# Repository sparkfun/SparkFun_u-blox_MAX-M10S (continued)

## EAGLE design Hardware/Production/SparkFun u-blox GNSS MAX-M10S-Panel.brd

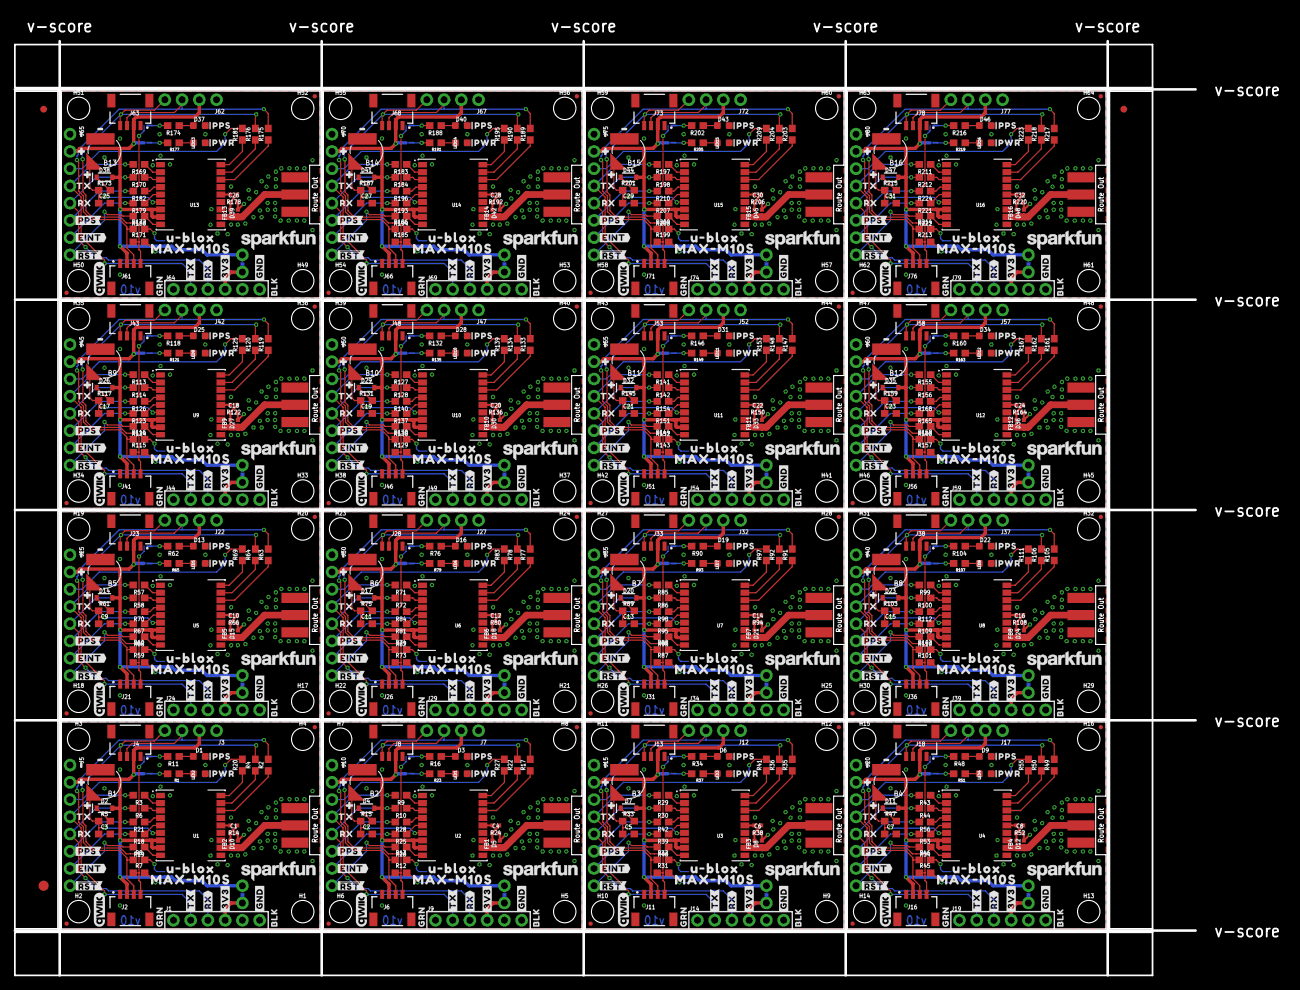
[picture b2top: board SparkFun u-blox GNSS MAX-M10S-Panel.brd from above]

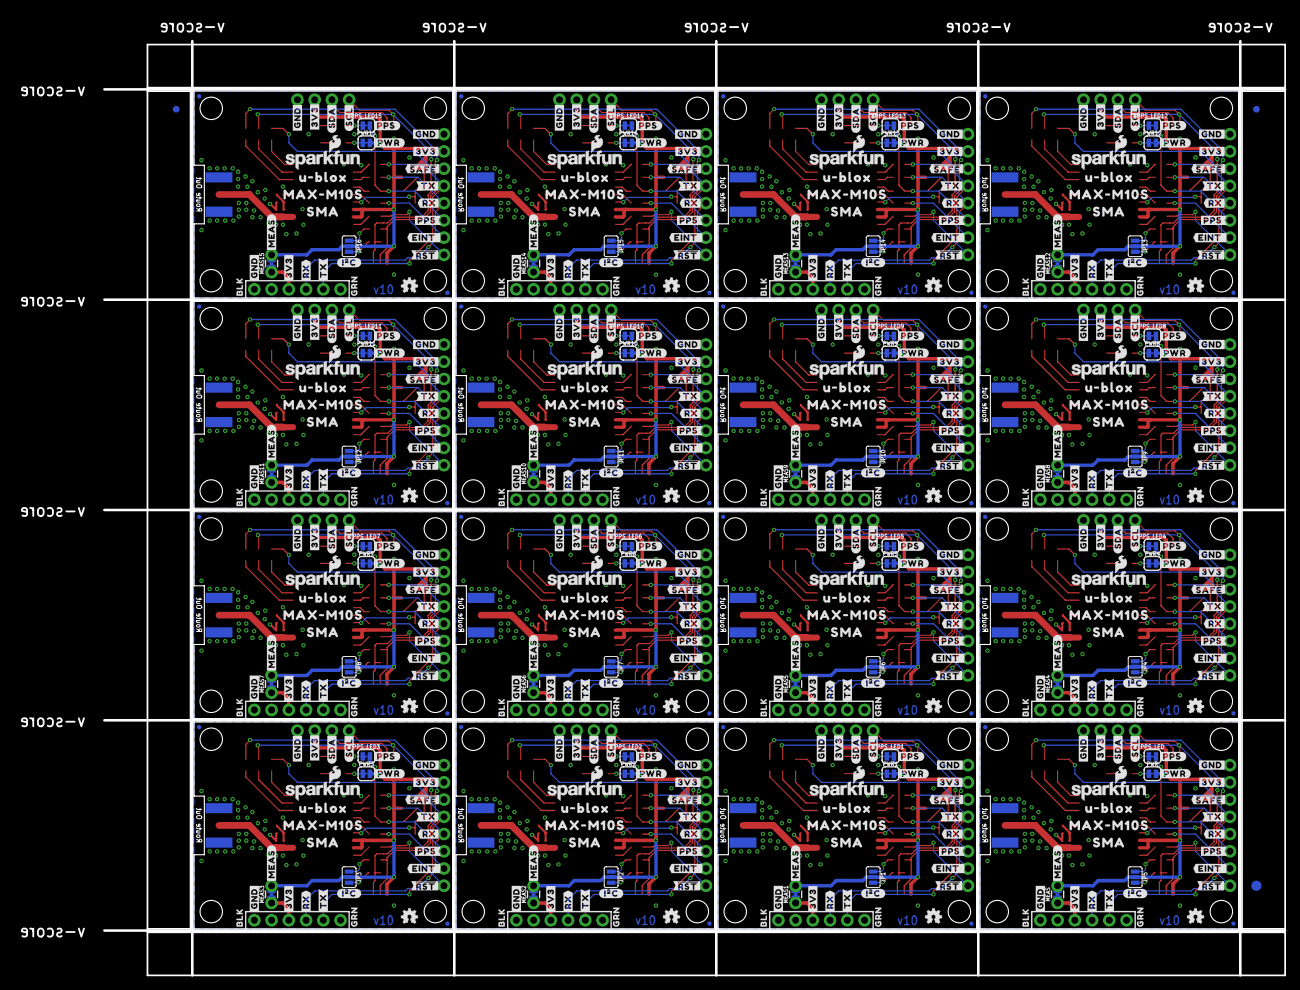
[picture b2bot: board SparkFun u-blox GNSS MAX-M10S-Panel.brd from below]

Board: 2 copper layers, 187.2 x 141.5 mm, 1430 parts (531 on the bottom side), 480 nets.

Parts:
B1, B2, B3, B4, B5, B6, B7, B8, B9, B10, B11, B12, B13, B14, B15, B16: 6.8MM_COIN_CELL; ML414H_IV01E
C1, C4, C6, C8, C10, C12, C14, C16, C18, C20, C22, C24, C26, C28, C30, C32: 47pF; 0402-TIGHT
C2, C3, C5, C7, C9, C11, C13, C15, C17, C19, C21, C23, C25, C27, C29, C31: 1.0uF; 0603
D1, D3, D6, D9, D13, D16, D19, D22, D25, D28, D31, D34, D37, D40, D43, D46: Yellow; LED-0603
D2, D4, D7, D11, D14, D17, D20, D23, D26, D29, D32, D35, D38, D41, D44, D47: 0.5A/40V/420mV; SOD-323
D5, D8, D10, D12, D15, D18, D21, D24, D27, D30, D33, D36, D39, D42, D45, D48: PESD0402-0402T; 0402-TIGHT
E1, E2, E3, E4, E5, E6, E7, E8, E9, E10, E11, E12, E13, E14, E15, E16: ANTENNA-SMA-GROUNDEDEDGE_SMA; SMA-EDGE
E$1, E$2, E$3, E$4: FIDUCIAL-1X2
E$5, E$6: FIDUCIAL-1.5X3
FB1, FB2, FB3, FB4, FB5, FB6, FB7, FB8, FB9, FB10, FB11, FB12, FB13, FB14, FB15, FB16: 2.66Ω; 0402-TIGHT
FD1, FD2, FD3, FD4, FD5, FD6, FD7, FD8, FD9, FD10, FD11, FD12, FD13, FD14, FD15, FD16, FD17, FD18, FD19, FD20, FD21, FD22, FD23, FD24, FD25, FD26, FD27, FD28, FD29, FD30, FD31, FD32, FD33, FD34, FD35, FD36, FD37, FD38, FD39, FD40, FD41, FD42, FD43, FD44, FD45, FD46, FD47, FD48, FD49, FD50, FD51, FD52, FD53, FD54, FD55, FD56, FD57, FD58, FD59, FD60, FD61, FD62, FD63, FD64: FIDUCIALUFIDUCIAL; FIDUCIAL-MICRO
H1, H2, H3, H4, H5, H6, H7, H8, H9, H10, H11, H12, H13, H14, H15, H16, H17, H18, H19, H20, H21, H22, H23, H24, H25, H26, H27, H28, H29, H30, H31, H32, H33, H34, H35, H36, H37, H38, H39, H40, H41, H42, H43, H44, H45, H46, H47, H48, H49, H50, H51, H52, H53, H54, H55, H56, H57, H58, H59, H60, H61, H62, H63, H64: STAND-OFF
J1, J9, J14, J19, J24, J29, J34, J39, J44, J49, J54, J59, J64, J69, J74, J79: USB-to-Serial; 1X06_NO_SILK
J2, J4, J6, J8, J11, J13, J16, J18, J21, J23, J26, J28, J31, J33, J36, J38, J41, J43, J46, J48, J51, J53, J56, J58, J61, J63, J66, J68, J71, J73, J76, J78: Qwiic RA; JST04_1MM_RA
J3, J7, J12, J17, J22, J27, J32, J37, J42, J47, J52, J57, J62, J67, J72, J77: PTH; 1X04_NO_SILK
J5, J10, J15, J20, J25, J30, J35, J40, J45, J50, J55, J60, J65, J70, J75, J80: 1X08_NO_SILK
JP1, JP2, JP3, JP4, JP5, JP6, JP7, JP8, JP9, JP10, JP11, JP12, JP13, JP14, JP15, JP16: JUMPER-SMT_3_NO_SILK; SMT-JUMPER_3_NO_SILK
LED1, LED2, LED3, LED4, LED5, LED6, LED7, LED8, LED9, LED10, LED11, LED12, LED13, LED14, LED15, LED16: RED; LED-0603
LOGO1, LOGO5, LOGO9, LOGO13, LOGO17, LOGO21, LOGO25, LOGO29, LOGO33, LOGO37, LOGO41, LOGO45, LOGO49, LOGO53, LOGO57, LOGO61: OSHW-LOGOMINI; OSHW-LOGO-MINI
LOGO2, LOGO6, LOGO10, LOGO14, LOGO18, LOGO22, LOGO26, LOGO30, LOGO34, LOGO38, LOGO42, LOGO46, LOGO50, LOGO54, LOGO58, LOGO62: SFE_LOGO_NAME_FLAME.1_INCH; SFE_LOGO_NAME_FLAME_.1
LOGO3, LOGO7, LOGO11, LOGO15, LOGO19, LOGO23, LOGO27, LOGO31, LOGO35, LOGO39, LOGO43, LOGO47, LOGO51, LOGO55, LOGO59, LOGO63: QWIIC_LOGO_5MM; QWIIC_5MM
LOGO4, LOGO8, LOGO12, LOGO16, LOGO20, LOGO24, LOGO28, LOGO32, LOGO36, LOGO40, LOGO44, LOGO48, LOGO52, LOGO56, LOGO60, LOGO64: SFE_LOGO_NAME.1_INCH; SFE_LOGO_NAME_.1
MEAS, MEAS1, MEAS2, MEAS3, MEAS4, MEAS5, MEAS6, MEAS7, MEAS8, MEAS9, MEAS10, MEAS11, MEAS12, MEAS13, MEAS14, MEAS15: JUMPER-COMBO_2_NC_TRACE; COMBO-JUMPER_2_NC_TRACE
PPS_LED, PPS_LED1, PPS_LED2, PPS_LED3, PPS_LED4, PPS_LED5, PPS_LED6, PPS_LED7, PPS_LED8, PPS_LED9, PPS_LED10, PPS_LED11, PPS_LED12, PPS_LED13, PPS_LED14, PPS_LED15: JUMPER-SMT_2_NC_TRACE_SILK; SMT-JUMPER_2_NC_TRACE_SILK
PWR, PWR1, PWR2, PWR3, PWR4, PWR5, PWR6, PWR7, PWR8, PWR9, PWR10, PWR11, PWR12, PWR13, PWR14, PWR15: JUMPER-SMT_2_NC_TRACE_SILK; SMT-JUMPER_2_NC_TRACE_SILK
R1, R11, R16, R23, R34, R37, R48, R51, R62, R65, R76, R79, R90, R93, R104, R107, R118, R121, R132, R135, R146, R149, R160, R163, R174, R177, R188, R191, R202, R205, R216, R219: 1k; 0603
R2, R3, R4, R6, R9, R10, R17, R18, R19, R20, R21, R22, R25, R26, R27, R28, R29, R30, R35, R36, R39, R40, R41, R42, R43, R44, R49, R50, R53, R54, R55, R56, R57, R58, R63, R64, R67, R68, R69, R70, R71, R72, R77, R78, R81, R82, R83, R84, R85, R86, R91, R92, R95, R96, R97, R98, R99, R100, R105, R106, R109, R110, R111, R112, R113, R114, R119, R120, R123, R124, R125, R126, R127, R128, R133, R134, R137, R138, R139, R140, R141, R142, R147, R148, R151, R152, R153, R154, R155, R156, R161, R162, R165, R166, R167, R168, R169, R170, R175, R176, R179, R180, R181, R182, R183, R184, R189, R190, R193, R194, R195, R196, R197, R198, R203, R204, R207, R208, R209, R210, R211, R212, R217, R218, R221, R222, R223, R224: 33; 0603
R5, R15, R33, R47, R61, R75, R89, R103, R117, R131, R145, R159, R173, R187, R201, R215: 3.3k; 0603
R7, R8, R12, R13, R31, R32, R45, R46, R59, R60, R73, R74, R87, R88, R101, R102, R115, R116, R129, R130, R143, R144, R157, R158, R171, R172, R185, R186, R199, R200, R213, R214: 2.2k; 0603
R14, R24, R38, R52, R66, R80, R94, R108, R122, R136, R150, R164, R178, R192, R206, R220: 33OHM-0402T-1/10W-1%; 0402-TIGHT
U1, U2, U3, U4, U5, U6, U7, U8, U9, U10, U11, U12, U13, U14, U15, U16: MAX-M10S
U$1, U$2, U$10, U$26, U$31, U$53, U$67, U$74, U$89, U$97, U$111, U$118, U$133, U$141, U$155, U$162, U$177, U$185, U$199, U$206, U$221, U$229, U$243, U$250, U$265, U$273, U$287, U$294, U$309, U$317, U$331, U$338, U$353, U$361, U$375, U$382, U$397, U$405, U$419, U$426, U$441, U$449, U$463, U$470, U$485, U$493, U$507, U$514, U$529, U$537, U$551, U$558, U$573, U$581, U$595, U$602, U$617, U$625, U$639, U$646, U$661, U$669, U$683, U$690: #3V3#4
U$3, U$11, U$17, U$27, U$34, U$54, U$68, U$75, U$90, U$98, U$112, U$119, U$134, U$142, U$156, U$163, U$178, U$186, U$200, U$207, U$222, U$230, U$244, U$251, U$266, U$274, U$288, U$295, U$310, U$318, U$332, U$339, U$354, U$362, U$376, U$383, U$398, U$406, U$420, U$427, U$442, U$450, U$464, U$471, U$486, U$494, U$508, U$515, U$530, U$538, U$552, U$559, U$574, U$582, U$596, U$603, U$618, U$626, U$640, U$647, U$662, U$670, U$684, U$691: #GND#5
U$4, U$28, U$47, U$69, U$91, U$113, U$135, U$157, U$179, U$201, U$223, U$245, U$267, U$289, U$311, U$333, U$355, U$377, U$399, U$421, U$443, U$465, U$487, U$509, U$531, U$553, U$575, U$597, U$619, U$641, U$663, U$685: BLK0
U$5, U$29, U$48, U$70, U$92, U$114, U$136, U$158, U$180, U$202, U$224, U$246, U$268, U$290, U$312, U$334, U$356, U$378, U$400, U$422, U$444, U$466, U$488, U$510, U$532, U$554, U$576, U$598, U$620, U$642, U$664, U$686: GRN1
U$6, U$49, U$93, U$137, U$181, U$225, U$269, U$313, U$357, U$401, U$445, U$489, U$533, U$577, U$621, U$665: PPS7
U$7, U$50, U$94, U$138, U$182, U$226, U$270, U$314, U$358, U$402, U$446, U$490, U$534, U$578, U$622, U$666: PWR6
U$8, U$25, U$51, U$66, U$95, U$110, U$139, U$154, U$183, U$198, U$227, U$242, U$271, U$286, U$315, U$330, U$359, U$374, U$403, U$418, U$447, U$462, U$491, U$506, U$535, U$550, U$579, U$594, U$623, U$638, U$667, U$682: #RX#2
U$9, U$22, U$52, U$65, U$96, U$109, U$140, U$153, U$184, U$197, U$228, U$241, U$272, U$285, U$316, U$329, U$360, U$373, U$404, U$417, U$448, U$461, U$492, U$505, U$536, U$549, U$580, U$593, U$624, U$637, U$668, U$681: #TX#3
U$12, U$55, U$99, U$143, U$187, U$231, U$275, U$319, U$363, U$407, U$451, U$495, U$539, U$583, U$627, U$671: ##RST##2
U$13, U$56, U$100, U$144, U$188, U$232, U$276, U$320, U$364, U$408, U$452, U$496, U$540, U$584, U$628, U$672: ##SAFE##0
U$14, U$43, U$57, U$82, U$101, U$126, U$145, U$170, U$189, U$214, U$233, U$258, U$277, U$302, U$321, U$346, U$365, U$390, U$409, U$434, U$453, U$478, U$497, U$522, U$541, U$566, U$585, U$610, U$629, U$654, U$673, U$698: #PPS#1
U$15, U$58, U$102, U$146, U$190, U$234, U$278, U$322, U$366, U$410, U$454, U$498, U$542, U$586, U$630, U$674: #RX#1
U$16, U$59, U$103, U$147, U$191, U$235, U$279, U$323, U$367, U$411, U$455, U$499, U$543, U$587, U$631, U$675: #TX#0
U$18, U$23, U$60, U$63, U$104, U$107, U$148, U$151, U$192, U$195, U$236, U$239, U$280, U$283, U$324, U$327, U$368, U$371, U$412, U$415, U$456, U$459, U$500, U$503, U$544, U$547, U$588, U$591, U$632, U$635, U$676, U$679: MAX#M10S1
U$19, U$37, U$78, U$85, U$122, U$129, U$166, U$173, U$210, U$217, U$254, U$261, U$298, U$305, U$342, U$349, U$386, U$393, U$430, U$437, U$474, U$481, U$518, U$525, U$562, U$569, U$606, U$613, U$650, U$657, U$694, U$701: #0
U$20, U$21, U$61, U$62, U$105, U$106, U$149, U$150, U$193, U$194, U$237, U$238, U$281, U$282, U$325, U$326, U$369, U$370, U$413, U$414, U$457, U$458, U$501, U$502, U$545, U$546, U$589, U$590, U$633, U$634, U$677, U$678: U#BLOX0
U$24, U$64, U$108, U$152, U$196, U$240, U$284, U$328, U$372, U$416, U$460, U$504, U$548, U$592, U$636, U$680: SMA2
U$30, U$71, U$115, U$159, U$203, U$247, U$291, U$335, U$379, U$423, U$467, U$511, U$555, U$599, U$643, U$687: #I�C#0
U$32, U$72, U$116, U$160, U$204, U$248, U$292, U$336, U$380, U$424, U$468, U$512, U$556, U$600, U$644, U$688: #SCL#1
U$33, U$73, U$117, U$161, U$205, U$249, U$293, U$337, U$381, U$425, U$469, U$513, U$557, U$601, U$645, U$689: #SDA#0
U$35, U$76, U$120, U$164, U$208, U$252, U$296, U$340, U$384, U$428, U$472, U$516, U$560, U$604, U$648, U$692: #PPS#0
U$36, U$77, U$121, U$165, U$209, U$253, U$297, U$341, U$385, U$429, U$473, U$517, U$561, U$605, U$649, U$693: #PWR#0
U$38, U$40, U$79, U$86, U$123, U$130, U$167, U$174, U$211, U$218, U$255, U$262, U$299, U$306, U$343, U$350, U$387, U$394, U$431, U$438, U$475, U$482, U$519, U$526, U$563, U$570, U$607, U$614, U$651, U$658, U$695, U$702: #1
U$39, U$80, U$124, U$168, U$212, U$256, U$300, U$344, U$388, U$432, U$476, U$520, U$564, U$608, U$652, U$696: ##RST##0
U$41, U$87, U$131, U$175, U$219, U$263, U$307, U$351, U$395, U$439, U$483, U$527, U$571, U$615, U$659, U$703: #MEAS#0
U$42, U$81, U$125, U$169, U$213, U$257, U$301, U$345, U$389, U$433, U$477, U$521, U$565, U$609, U$653, U$697: #EINT#0
U$44, U$83, U$127, U$171, U$215, U$259, U$303, U$347, U$391, U$435, U$479, U$523, U$567, U$611, U$655, U$699: RX2
U$45, U$84, U$128, U$172, U$216, U$260, U$304, U$348, U$392, U$436, U$480, U$524, U$568, U$612, U$656, U$700: TX3
U$46, U$88, U$132, U$176, U$220, U$264, U$308, U$352, U$396, U$440, U$484, U$528, U$572, U$616, U$660, U$704: #EINT_#0

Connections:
3.3V: D2.A, J2.2, J3.2, J4.2, J5.2, JP5.2, MEAS.2, MEAS.4, PWR.2, U1.7, U1.8
3.3V1: D4.A, J6.2, J7.2, J8.2, J10.2, JP1.2, MEAS1.2, MEAS1.4, PWR1.2, U2.7, U2.8
3.3V2: D7.A, J11.2, J12.2, J13.2, J15.2, JP2.2, MEAS2.2, MEAS2.4, PWR2.2, U3.7, U3.8
3.3V3: D11.A, J16.2, J17.2, J18.2, J20.2, JP3.2, MEAS3.2, MEAS3.4, PWR3.2, U4.7, U4.8
3.3V4: D14.A, J21.2, J22.2, J23.2, J25.2, JP4.2, MEAS4.2, MEAS4.4, PWR4.2, U5.7, U5.8
3.3V5: D17.A, J26.2, J27.2, J28.2, J30.2, JP6.2, MEAS5.2, MEAS5.4, PWR5.2, U6.7, U6.8
3.3V6: D20.A, J31.2, J32.2, J33.2, J35.2, JP7.2, MEAS6.2, MEAS6.4, PWR6.2, U7.7, U7.8
3.3V7: D23.A, J36.2, J37.2, J38.2, J40.2, JP8.2, MEAS7.2, MEAS7.4, PWR7.2, U8.7, U8.8
3.3V8: D26.A, J41.2, J42.2, J43.2, J45.2, JP9.2, MEAS8.2, MEAS8.4, PWR8.2, U9.7, U9.8
3.3V9: D29.A, J46.2, J47.2, J48.2, J50.2, JP10.2, MEAS9.2, MEAS9.4, PWR9.2, U10.7, U10.8
3.3V10: D32.A, J51.2, J52.2, J53.2, J55.2, JP11.2, MEAS10.2, MEAS10.4, PWR10.2, U11.7, U11.8
3.3V11: D35.A, J56.2, J57.2, J58.2, J60.2, JP12.2, MEAS11.2, MEAS11.4, PWR11.2, U12.7, U12.8
3.3V12: D38.A, J61.2, J62.2, J63.2, J65.2, JP13.2, MEAS12.2, MEAS12.4, PWR12.2, U13.7, U13.8
3.3V13: D41.A, J66.2, J67.2, J68.2, J70.2, JP14.2, MEAS13.2, MEAS13.4, PWR13.2, U14.7, U14.8
3.3V14: D44.A, J71.2, J72.2, J73.2, J75.2, JP15.2, MEAS14.2, MEAS14.4, PWR14.2, U15.7, U15.8
3.3V15: D47.A, J76.2, J77.2, J78.2, J80.2, JP16.2, MEAS15.2, MEAS15.4, PWR15.2, U16.7, U16.8
!RESET: J5.8, R19.2
!RESET1: J10.8, R26.2
!RESET2: J15.8, R40.2
!RESET3: J20.8, R54.2
!RESET4: J25.8, R68.2
!RESET5: J30.8, R82.2
!RESET6: J35.8, R96.2
!RESET7: J40.8, R110.2
!RESET8: J45.8, R124.2
!RESET9: J50.8, R138.2
!RESET10: J55.8, R152.2
!RESET11: J60.8, R166.2
!RESET12: J65.8, R180.2
!RESET13: J70.8, R194.2
!RESET14: J75.8, R208.2
!RESET15: J80.8, R222.2
!SAFE: J5.3, R20.2
!SAFE1: J10.3, R27.2
!SAFE2: J15.3, R41.2
!SAFE3: J20.3, R55.2
!SAFE4: J25.3, R69.2
!SAFE5: J30.3, R83.2
!SAFE6: J35.3, R97.2
!SAFE7: J40.3, R111.2
!SAFE8: J45.3, R125.2
!SAFE9: J50.3, R139.2
!SAFE10: J55.3, R153.2
!SAFE11: J60.3, R167.2
!SAFE12: J65.3, R181.2
!SAFE13: J70.3, R195.2
!SAFE14: J75.3, R209.2
!SAFE15: J80.3, R223.2
ANT_VCC: C1.1, FB2.2, R14.1
ANT_VCC1: C4.1, FB1.2, R24.1
ANT_VCC2: C6.1, FB3.2, R38.1
ANT_VCC3: C8.1, FB4.2, R52.1
ANT_VCC4: C10.1, FB5.2, R66.1
ANT_VCC5: C12.1, FB6.2, R80.1
ANT_VCC6: C14.1, FB7.2, R94.1
ANT_VCC7: C16.1, FB8.2, R108.1
ANT_VCC8: C18.1, FB9.2, R122.1
ANT_VCC9: C20.1, FB10.2, R136.1
ANT_VCC10: C22.1, FB11.2, R150.1
ANT_VCC11: C24.1, FB12.2, R164.1
ANT_VCC12: C26.1, FB13.2, R178.1
ANT_VCC13: C28.1, FB14.2, R192.1
ANT_VCC14: C30.1, FB15.2, R206.1
ANT_VCC15: C32.1, FB16.2, R220.1
BACKUP: B1.+, C3.1, R5.1, U1.6
BACKUP1: B2.+, C2.1, R15.1, U2.6
BACKUP2: B3.+, C5.1, R33.1, U3.6
BACKUP3: B4.+, C7.1, R47.1, U4.6
BACKUP4: B5.+, C9.1, R61.1, U5.6
BACKUP5: B6.+, C11.1, R75.1, U6.6
BACKUP6: B7.+, C13.1, R89.1, U7.6
BACKUP7: B8.+, C15.1, R103.1, U8.6
BACKUP8: B9.+, C17.1, R117.1, U9.6
BACKUP9: B10.+, C19.1, R131.1, U10.6
BACKUP10: B11.+, C21.1, R145.1, U11.6
BACKUP11: B12.+, C23.1, R159.1, U12.6
BACKUP12: B13.+, C25.1, R173.1, U13.6
BACKUP13: B14.+, C27.1, R187.1, U14.6
BACKUP14: B15.+, C29.1, R201.1, U15.6
BACKUP15: B16.+, C31.1, R215.1, U16.6
EXTINT_LV: R18.1, U1.5
EXTINT_LV1: R25.1, U2.5
EXTINT_LV2: R39.1, U3.5
EXTINT_LV3: R53.1, U4.5
EXTINT_LV4: R67.1, U5.5
EXTINT_LV5: R81.1, U6.5
EXTINT_LV6: R95.1, U7.5
EXTINT_LV7: R109.1, U8.5
EXTINT_LV8: R123.1, U9.5
EXTINT_LV9: R137.1, U10.5
EXTINT_LV10: R151.1, U11.5
EXTINT_LV11: R165.1, U12.5
EXTINT_LV12: R179.1, U13.5
EXTINT_LV13: R193.1, U14.5
EXTINT_LV14: R207.1, U15.5
EXTINT_LV15: R221.1, U16.5
GND: B1.-, C1.2, C3.2, D1.C, D10.2, E1.GND@0, E1.GND@1, E1.GND@2, E1.GND@3, J1.6, J2.1, J3.1, J4.1, J5.1, LED2.C, U1.1, U1.10, U1.12
GND1: B2.-, C2.2, C4.2, D3.C, D5.2, E2.GND@0, E2.GND@1, E2.GND@2, E2.GND@3, J6.1, J7.1, J8.1, J9.6, J10.1, LED1.C, U2.1, U2.10, U2.12
GND2: B3.-, C5.2, C6.2, D6.C, D8.2, E3.GND@0, E3.GND@1, E3.GND@2, E3.GND@3, J11.1, J12.1, J13.1, J14.6, J15.1, LED3.C, U3.1, U3.10, U3.12
GND3: B4.-, C7.2, C8.2, D9.C, D12.2, E4.GND@0, E4.GND@1, E4.GND@2, E4.GND@3, J16.1, J17.1, J18.1, J19.6, J20.1, LED4.C, U4.1, U4.10, U4.12
GND4: B5.-, C9.2, C10.2, D13.C, D15.2, E5.GND@0, E5.GND@1, E5.GND@2, E5.GND@3, J21.1, J22.1, J23.1, J24.6, J25.1, LED5.C, U5.1, U5.10, U5.12
GND5: B6.-, C11.2, C12.2, D16.C, D18.2, E6.GND@0, E6.GND@1, E6.GND@2, E6.GND@3, J26.1, J27.1, J28.1, J29.6, J30.1, LED6.C, U6.1, U6.10, U6.12
GND6: B7.-, C13.2, C14.2, D19.C, D21.2, E7.GND@0, E7.GND@1, E7.GND@2, E7.GND@3, J31.1, J32.1, J33.1, J34.6, J35.1, LED7.C, U7.1, U7.10, U7.12
GND7: B8.-, C15.2, C16.2, D22.C, D24.2, E8.GND@0, E8.GND@1, E8.GND@2, E8.GND@3, J36.1, J37.1, J38.1, J39.6, J40.1, LED8.C, U8.1, U8.10, U8.12
GND8: B9.-, C17.2, C18.2, D25.C, D27.2, E9.GND@0, E9.GND@1, E9.GND@2, E9.GND@3, J41.1, J42.1, J43.1, J44.6, J45.1, LED9.C, U9.1, U9.10, U9.12
GND9: B10.-, C19.2, C20.2, D28.C, D30.2, E10.GND@0, E10.GND@1, E10.GND@2, E10.GND@3, J46.1, J47.1, J48.1, J49.6, J50.1, LED10.C, U10.1, U10.10, U10.12
GND10: B11.-, C21.2, C22.2, D31.C, D33.2, E11.GND@0, E11.GND@1, E11.GND@2, E11.GND@3, J51.1, J52.1, J53.1, J54.6, J55.1, LED11.C, U11.1, U11.10, U11.12
GND11: B12.-, C23.2, C24.2, D34.C, D36.2, E12.GND@0, E12.GND@1, E12.GND@2, E12.GND@3, J56.1, J57.1, J58.1, J59.6, J60.1, LED12.C, U12.1, U12.10, U12.12
GND12: B13.-, C25.2, C26.2, D37.C, D39.2, E13.GND@0, E13.GND@1, E13.GND@2, E13.GND@3, J61.1, J62.1, J63.1, J64.6, J65.1, LED13.C, U13.1, U13.10, U13.12
GND13: B14.-, C27.2, C28.2, D40.C, D42.2, E14.GND@0, E14.GND@1, E14.GND@2, E14.GND@3, J66.1, J67.1, J68.1, J69.6, J70.1, LED14.C, U14.1, U14.10, U14.12
GND14: B15.-, C29.2, C30.2, D43.C, D45.2, E15.GND@0, E15.GND@1, E15.GND@2, E15.GND@3, J71.1, J72.1, J73.1, J74.6, J75.1, LED15.C, U15.1, U15.10, U15.12
GND15: B16.-, C31.2, C32.2, D46.C, D48.2, E16.GND@0, E16.GND@1, E16.GND@2, E16.GND@3, J76.1, J77.1, J78.1, J79.6, J80.1, LED16.C, U16.1, U16.10, U16.12
GPS_RF: D10.1, E1.SIG, FB2.1, U1.11
GPS_RF1: D5.1, E2.SIG, FB1.1, U2.11
GPS_RF2: D8.1, E3.SIG, FB3.1, U3.11
GPS_RF3: D12.1, E4.SIG, FB4.1, U4.11
GPS_RF4: D15.1, E5.SIG, FB5.1, U5.11
GPS_RF5: D18.1, E6.SIG, FB6.1, U6.11
GPS_RF6: D21.1, E7.SIG, FB7.1, U7.11
GPS_RF7: D24.1, E8.SIG, FB8.1, U8.11
GPS_RF8: D27.1, E9.SIG, FB9.1, U9.11
GPS_RF9: D30.1, E10.SIG, FB10.1, U10.11
GPS_RF10: D33.1, E11.SIG, FB11.1, U11.11
GPS_RF11: D36.1, E12.SIG, FB12.1, U12.11
GPS_RF12: D39.1, E13.SIG, FB13.1, U13.11
GPS_RF13: D42.1, E14.SIG, FB14.1, U14.11
GPS_RF14: D45.1, E15.SIG, FB15.1, U15.11
GPS_RF15: D48.1, E16.SIG, FB16.1, U16.11
INT: J5.7, R18.2
INT1: J10.7, R25.2
INT2: J15.7, R39.2
INT3: J20.7, R53.2
INT4: J25.7, R67.2
INT5: J30.7, R81.2
INT6: J35.7, R95.2
INT7: J40.7, R109.2
INT8: J45.7, R123.2
INT9: J50.7, R137.2
INT10: J55.7, R151.2
INT11: J60.7, R165.2
INT12: J65.7, R179.2
INT13: J70.7, R193.2
INT14: J75.7, R207.2
INT15: J80.7, R221.2
unnamed: J1.4, MEAS.1, MEAS.3
unnamed: D1.A, R11.1
unnamed: JP1.1, R13.2
unnamed: PPS_LED.1, R11.2
unnamed: JP5.1, R8.2
unnamed: D2.C, R5.2
unnamed: JP1.3, R12.2
unnamed: JP5.3, R7.2
unnamed: D3.A, R16.1
unnamed: LED2.A, R1.1
unnamed: PPS_LED1.1, R16.2
unnamed: D4.C, R15.2
unnamed: LED1.A, R23.1
unnamed: PWR1.1, R23.2
unnamed: J9.4, MEAS1.1, MEAS1.3
unnamed: JP2.1, R32.2
unnamed: PWR.1, R1.2
unnamed: JP2.3, R31.2
unnamed: D6.A, R34.1
unnamed: PPS_LED2.1, R34.2
unnamed: D7.C, R33.2
unnamed: LED3.A, R37.1
unnamed: PWR2.1, R37.2
unnamed: J14.4, MEAS2.1, MEAS2.3
unnamed: JP3.1, R46.2
unnamed: JP3.3, R45.2
unnamed: D9.A, R48.1
unnamed: PPS_LED3.1, R48.2
unnamed: D11.C, R47.2
unnamed: LED4.A, R51.1
unnamed: PWR3.1, R51.2
unnamed: J19.4, MEAS3.1, MEAS3.3
unnamed: JP4.1, R60.2
unnamed: JP4.3, R59.2
unnamed: D13.A, R62.1
unnamed: PPS_LED4.1, R62.2
unnamed: D14.C, R61.2
unnamed: LED5.A, R65.1
unnamed: PWR4.1, R65.2
unnamed: J24.4, MEAS4.1, MEAS4.3
unnamed: JP6.1, R74.2
unnamed: JP6.3, R73.2
unnamed: D16.A, R76.1
unnamed: PPS_LED5.1, R76.2
unnamed: D17.C, R75.2
unnamed: LED6.A, R79.1
unnamed: PWR5.1, R79.2
unnamed: J29.4, MEAS5.1, MEAS5.3
unnamed: JP7.1, R88.2
unnamed: JP7.3, R87.2
unnamed: D19.A, R90.1
unnamed: PPS_LED6.1, R90.2
unnamed: D20.C, R89.2
unnamed: LED7.A, R93.1
unnamed: PWR6.1, R93.2
unnamed: J34.4, MEAS6.1, MEAS6.3
unnamed: JP8.1, R102.2
unnamed: JP8.3, R101.2
unnamed: D22.A, R104.1
unnamed: PPS_LED7.1, R104.2
unnamed: D23.C, R103.2
unnamed: LED8.A, R107.1
unnamed: PWR7.1, R107.2
unnamed: J39.4, MEAS7.1, MEAS7.3
unnamed: JP9.1, R116.2
unnamed: JP9.3, R115.2
unnamed: D25.A, R118.1
unnamed: PPS_LED8.1, R118.2
unnamed: D26.C, R117.2
unnamed: LED9.A, R121.1
unnamed: PWR8.1, R121.2
unnamed: J44.4, MEAS8.1, MEAS8.3
unnamed: JP10.1, R130.2
unnamed: JP10.3, R129.2
unnamed: D28.A, R132.1
unnamed: PPS_LED9.1, R132.2
unnamed: D29.C, R131.2
unnamed: LED10.A, R135.1
unnamed: PWR9.1, R135.2
unnamed: J49.4, MEAS9.1, MEAS9.3
unnamed: JP11.1, R144.2
unnamed: JP11.3, R143.2
unnamed: D31.A, R146.1
unnamed: PPS_LED10.1, R146.2
unnamed: D32.C, R145.2
unnamed: LED11.A, R149.1
unnamed: PWR10.1, R149.2
unnamed: J54.4, MEAS10.1, MEAS10.3
unnamed: JP12.1, R158.2
unnamed: JP12.3, R157.2
unnamed: D34.A, R160.1
unnamed: PPS_LED11.1, R160.2
unnamed: D35.C, R159.2
unnamed: LED12.A, R163.1
unnamed: PWR11.1, R163.2
unnamed: J59.4, MEAS11.1, MEAS11.3
unnamed: JP13.1, R172.2
unnamed: JP13.3, R171.2
unnamed: D37.A, R174.1
unnamed: PPS_LED12.1, R174.2
unnamed: D38.C, R173.2
unnamed: LED13.A, R177.1
unnamed: PWR12.1, R177.2
unnamed: J64.4, MEAS12.1, MEAS12.3
unnamed: JP14.1, R186.2
unnamed: JP14.3, R185.2
unnamed: D40.A, R188.1
unnamed: PPS_LED13.1, R188.2
unnamed: D41.C, R187.2
unnamed: LED14.A, R191.1
unnamed: PWR13.1, R191.2
unnamed: J69.4, MEAS13.1, MEAS13.3
unnamed: JP15.1, R200.2
unnamed: JP15.3, R199.2
unnamed: D43.A, R202.1
unnamed: PPS_LED14.1, R202.2
unnamed: D44.C, R201.2
unnamed: LED15.A, R205.1
unnamed: PWR14.1, R205.2
unnamed: J74.4, MEAS14.1, MEAS14.3
unnamed: JP16.1, R214.2
unnamed: JP16.3, R213.2
unnamed: D46.A, R216.1
unnamed: PPS_LED15.1, R216.2
unnamed: D47.C, R215.2
unnamed: LED16.A, R219.1
unnamed: PWR15.1, R219.2
unnamed: J79.4, MEAS15.1, MEAS15.3
PPS: J5.6, PPS_LED.2, R21.2
PPS1: J10.6, PPS_LED1.2, R28.2
PPS2: J15.6, PPS_LED2.2, R42.2
PPS3: J20.6, PPS_LED3.2, R56.2
PPS4: J25.6, PPS_LED4.2, R70.2
PPS5: J30.6, PPS_LED5.2, R84.2
PPS6: J35.6, PPS_LED6.2, R98.2
PPS7: J40.6, PPS_LED7.2, R112.2
PPS8: J45.6, PPS_LED8.2, R126.2
PPS9: J50.6, PPS_LED9.2, R140.2
PPS10: J55.6, PPS_LED10.2, R154.2
PPS11: J60.6, PPS_LED11.2, R168.2
PPS12: J65.6, PPS_LED12.2, R182.2
PPS13: J70.6, PPS_LED13.2, R196.2
PPS14: J75.6, PPS_LED14.2, R210.2
PPS15: J80.6, PPS_LED15.2, R224.2
PPS_LV: R21.1, U1.4
PPS_LV1: R28.1, U2.4
PPS_LV2: R42.1, U3.4
PPS_LV3: R56.1, U4.4
PPS_LV4: R70.1, U5.4
PPS_LV5: R84.1, U6.4
PPS_LV6: R98.1, U7.4
PPS_LV7: R112.1, U8.4
PPS_LV8: R126.1, U9.4
PPS_LV9: R140.1, U10.4
PPS_LV10: R154.1, U11.4
PPS_LV11: R168.1, U12.4
PPS_LV12: R182.1, U13.4
PPS_LV13: R196.1, U14.4
PPS_LV14: R210.1, U15.4
PPS_LV15: R224.1, U16.4
RST_LV: R19.1, U1.9
RST_LV1: R26.1, U2.9
RST_LV2: R40.1, U3.9
RST_LV3: R54.1, U4.9
RST_LV4: R68.1, U5.9
RST_LV5: R82.1, U6.9
RST_LV6: R96.1, U7.9
RST_LV7: R110.1, U8.9
RST_LV8: R124.1, U9.9
RST_LV9: R138.1, U10.9
RST_LV10: R152.1, U11.9
RST_LV11: R166.1, U12.9
RST_LV12: R180.1, U13.9
RST_LV13: R194.1, U14.9
RST_LV14: R208.1, U15.9
RST_LV15: R222.1, U16.9
RXI: J1.3, J5.5, R6.2
RXI1: J9.3, J10.5, R10.2
RXI2: J14.3, J15.5, R30.2
RXI3: J19.3, J20.5, R44.2
RXI4: J24.3, J25.5, R58.2
RXI5: J29.3, J30.5, R72.2
RXI6: J34.3, J35.5, R86.2
RXI7: J39.3, J40.5, R100.2
RXI8: J44.3, J45.5, R114.2
RXI9: J49.3, J50.5, R128.2
RXI10: J54.3, J55.5, R142.2
RXI11: J59.3, J60.5, R156.2
RXI12: J64.3, J65.5, R170.2
RXI13: J69.3, J70.5, R184.2
RXI14: J74.3, J75.5, R198.2
RXI15: J79.3, J80.5, R212.2
RXLV: R6.1, U1.3
RXLV1: R10.1, U2.3
RXLV2: R30.1, U3.3
RXLV3: R44.1, U4.3
RXLV4: R58.1, U5.3
RXLV5: R72.1, U6.3
RXLV6: R86.1, U7.3
RXLV7: R100.1, U8.3
RXLV8: R114.1, U9.3
RXLV9: R128.1, U10.3
RXLV10: R142.1, U11.3
RXLV11: R156.1, U12.3
RXLV12: R170.1, U13.3
RXLV13: R184.1, U14.3
RXLV14: R198.1, U15.3
RXLV15: R212.1, U16.3
SAFE_LV: R20.1, U1.18
SAFE_LV1: R27.1, U2.18
SAFE_LV2: R41.1, U3.18
SAFE_LV3: R55.1, U4.18
SAFE_LV4: R69.1, U5.18
SAFE_LV5: R83.1, U6.18
SAFE_LV6: R97.1, U7.18
SAFE_LV7: R111.1, U8.18
SAFE_LV8: R125.1, U9.18
SAFE_LV9: R139.1, U10.18
SAFE_LV10: R153.1, U11.18
SAFE_LV11: R167.1, U12.18
SAFE_LV12: R181.1, U13.18
SAFE_LV13: R195.1, U14.18
SAFE_LV14: R209.1, U15.18
SAFE_LV15: R223.1, U16.18
SCL: J2.4, J3.4, J4.4, R4.2, R7.1
SCL1: J6.4, J7.4, J8.4, R12.1, R22.2
SCL2: J11.4, J12.4, J13.4, R31.1, R36.2
SCL3: J16.4, J17.4, J18.4, R45.1, R50.2
SCL4: J21.4, J22.4, J23.4, R59.1, R64.2
SCL5: J26.4, J27.4, J28.4, R73.1, R78.2
SCL6: J31.4, J32.4, J33.4, R87.1, R92.2
SCL7: J36.4, J37.4, J38.4, R101.1, R106.2
SCL8: J41.4, J42.4, J43.4, R115.1, R120.2
SCL9: J46.4, J47.4, J48.4, R129.1, R134.2
SCL10: J51.4, J52.4, J53.4, R143.1, R148.2
SCL11: J56.4, J57.4, J58.4, R157.1, R162.2
SCL12: J61.4, J62.4, J63.4, R171.1, R176.2
SCL13: J66.4, J67.4, J68.4, R185.1, R190.2
SCL14: J71.4, J72.4, J73.4, R199.1, R204.2
SCL15: J76.4, J77.4, J78.4, R213.1, R218.2
SCL_LV: R4.1, U1.17
SCL_LV1: R22.1, U2.17
SCL_LV2: R36.1, U3.17
SCL_LV3: R50.1, U4.17
SCL_LV4: R64.1, U5.17
SCL_LV5: R78.1, U6.17
SCL_LV6: R92.1, U7.17
SCL_LV7: R106.1, U8.17
SCL_LV8: R120.1, U9.17
SCL_LV9: R134.1, U10.17
SCL_LV10: R148.1, U11.17
SCL_LV11: R162.1, U12.17
SCL_LV12: R176.1, U13.17
SCL_LV13: R190.1, U14.17
SCL_LV14: R204.1, U15.17
SCL_LV15: R218.1, U16.17
SDA: J2.3, J3.3, J4.3, R2.2, R8.1
SDA1: J6.3, J7.3, J8.3, R13.1, R17.2
SDA2: J11.3, J12.3, J13.3, R32.1, R35.2
SDA3: J16.3, J17.3, J18.3, R46.1, R49.2
SDA4: J21.3, J22.3, J23.3, R60.1, R63.2
SDA5: J26.3, J27.3, J28.3, R74.1, R77.2
SDA6: J31.3, J32.3, J33.3, R88.1, R91.2
SDA7: J36.3, J37.3, J38.3, R102.1, R105.2
SDA8: J41.3, J42.3, J43.3, R116.1, R119.2
SDA9: J46.3, J47.3, J48.3, R130.1, R133.2
SDA10: J51.3, J52.3, J53.3, R144.1, R147.2
SDA11: J56.3, J57.3, J58.3, R158.1, R161.2
SDA12: J61.3, J62.3, J63.3, R172.1, R175.2
SDA13: J66.3, J67.3, J68.3, R186.1, R189.2
SDA14: J71.3, J72.3, J73.3, R200.1, R203.2
SDA15: J76.3, J77.3, J78.3, R214.1, R217.2
SDA_LV: R2.1, U1.16
SDA_LV1: R17.1, U2.16
SDA_LV2: R35.1, U3.16
SDA_LV3: R49.1, U4.16
SDA_LV4: R63.1, U5.16
SDA_LV5: R77.1, U6.16
SDA_LV6: R91.1, U7.16
SDA_LV7: R105.1, U8.16
SDA_LV8: R119.1, U9.16
SDA_LV9: R133.1, U10.16
SDA_LV10: R147.1, U11.16
SDA_LV11: R161.1, U12.16
SDA_LV12: R175.1, U13.16
SDA_LV13: R189.1, U14.16
SDA_LV14: R203.1, U15.16
SDA_LV15: R217.1, U16.16
TXLV: R3.1, U1.2
TXLV1: R9.1, U2.2
TXLV2: R29.1, U3.2
TXLV3: R43.1, U4.2
TXLV4: R57.1, U5.2
TXLV5: R71.1, U6.2
TXLV6: R85.1, U7.2
TXLV7: R99.1, U8.2
TXLV8: R113.1, U9.2
TXLV9: R127.1, U10.2
TXLV10: R141.1, U11.2
TXLV11: R155.1, U12.2
TXLV12: R169.1, U13.2
TXLV13: R183.1, U14.2
TXLV14: R197.1, U15.2
TXLV15: R211.1, U16.2
TXO: J1.2, J5.4, R3.2
TXO1: J9.2, J10.4, R9.2
TXO2: J14.2, J15.4, R29.2
TXO3: J19.2, J20.4, R43.2
TXO4: J24.2, J25.4, R57.2
TXO5: J29.2, J30.4, R71.2
TXO6: J34.2, J35.4, R85.2
TXO7: J39.2, J40.4, R99.2
TXO8: J44.2, J45.4, R113.2
TXO9: J49.2, J50.4, R127.2
TXO10: J54.2, J55.4, R141.2
TXO11: J59.2, J60.4, R155.2
TXO12: J64.2, J65.4, R169.2
TXO13: J69.2, J70.4, R183.2
TXO14: J74.2, J75.4, R197.2
TXO15: J79.2, J80.4, R211.2
VCC_RF: R14.2, U1.14
VCC_RF1: R24.2, U2.14
VCC_RF2: R38.2, U3.14
VCC_RF3: R52.2, U4.14
VCC_RF4: R66.2, U5.14
VCC_RF5: R80.2, U6.14
VCC_RF6: R94.2, U7.14
VCC_RF7: R108.2, U8.14
VCC_RF8: R122.2, U9.14
VCC_RF9: R136.2, U10.14
VCC_RF10: R150.2, U11.14
VCC_RF11: R164.2, U12.14
VCC_RF12: R178.2, U13.14
VCC_RF13: R192.2, U14.14
VCC_RF14: R206.2, U15.14
VCC_RF15: R220.2, U16.14

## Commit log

2021-03-10 Changing RF path to 0402. Adding GND vias on both RF trace sides. Adding panel.
2021-11-15 Add ESD RF diode. Change to PTH SMA.
2021-11-15 Add panel files
2022-10-19 Ported MAX-M10S Tutorial from Learn.SparkFun.com
2022-10-19 Index test
2022-10-20 update file names to fix links
2022-10-20 adjust relative links that point to images to GitHub Pages tutorial assets
2022-10-20 remove div tags that are breaking table
2022-10-20 Convert "Bootstrap notes" to "mkdocs markdown notes"
2022-10-20 Center Images
2022-10-20 Adjust navigation bar, page name
2022-10-20 adjust div style
2022-10-20 adjust div style for horizontal and vertical alignment
2022-10-20 Update Top and Left Side Navigation Bar
2022-10-20 adjust position of images and add big product "tile"
2022-10-20 adjust tables
2022-10-20 Fix whitespace
2022-10-20 remove unwanted div tag
2022-10-20 center Qwiic banner
2022-10-20 center Qwiic banner with <div>
2022-10-20 Adjust table style
2022-10-20 Convert boostrap buttons to mkdocs buttons
2022-10-20 Center buttons
2022-10-20 Adjust <div> to center button
2022-10-20 Adjust Spacing between <div> and markdown
2022-10-20 Adjust markdown into html tags
2022-10-20 adjust boostrap buttons to mkdocs buttons
2022-10-20 Adjust spacing so it doesn't render as code
2022-10-20 Test primary button color alternative
2022-10-20 adjust button attribute for alternative color
2022-10-20 Insert Learn.SparkFun.com tutorials as tutorial tiles in a grid
2022-10-26 Adjust formatting for tutorial tiles
2022-10-26 Adjust formatting for Product Tile
2023-08-21 Formatting Update
    Center all images used in tables by placing them in center and middle
2023-08-21 Deployed 2a072bc with MkDocs version: 1.5.2
2024-10-28 Add cookies
2024-10-29 Deployed 48faa7a with MkDocs version: 1.6.1
